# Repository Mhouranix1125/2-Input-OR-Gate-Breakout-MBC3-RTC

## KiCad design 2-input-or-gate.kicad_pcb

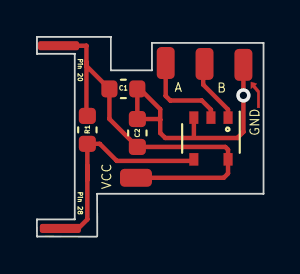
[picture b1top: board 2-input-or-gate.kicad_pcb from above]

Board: 2 copper layers, 12.6 x 11.1 mm, 4 parts (0 on the bottom side), 3 nets.

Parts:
C1: 0.01uf; C_0603_1608Metric
C2: 0.1uf; C_0603_1608Metric
R1: C_0603_1608Metric
U5: 74LVC1G332GW,125; TSOP-6_1.65x3.05mm_P0.95mm

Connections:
CE: R1.3, U5.4
GND: C1.6, C2.6, U5.3
VCC5V: C1.5, C2.5, R1.2, U5.6

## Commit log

2022-12-22 updated design to be larger with larger pads. Got rid of 1k resistor.
